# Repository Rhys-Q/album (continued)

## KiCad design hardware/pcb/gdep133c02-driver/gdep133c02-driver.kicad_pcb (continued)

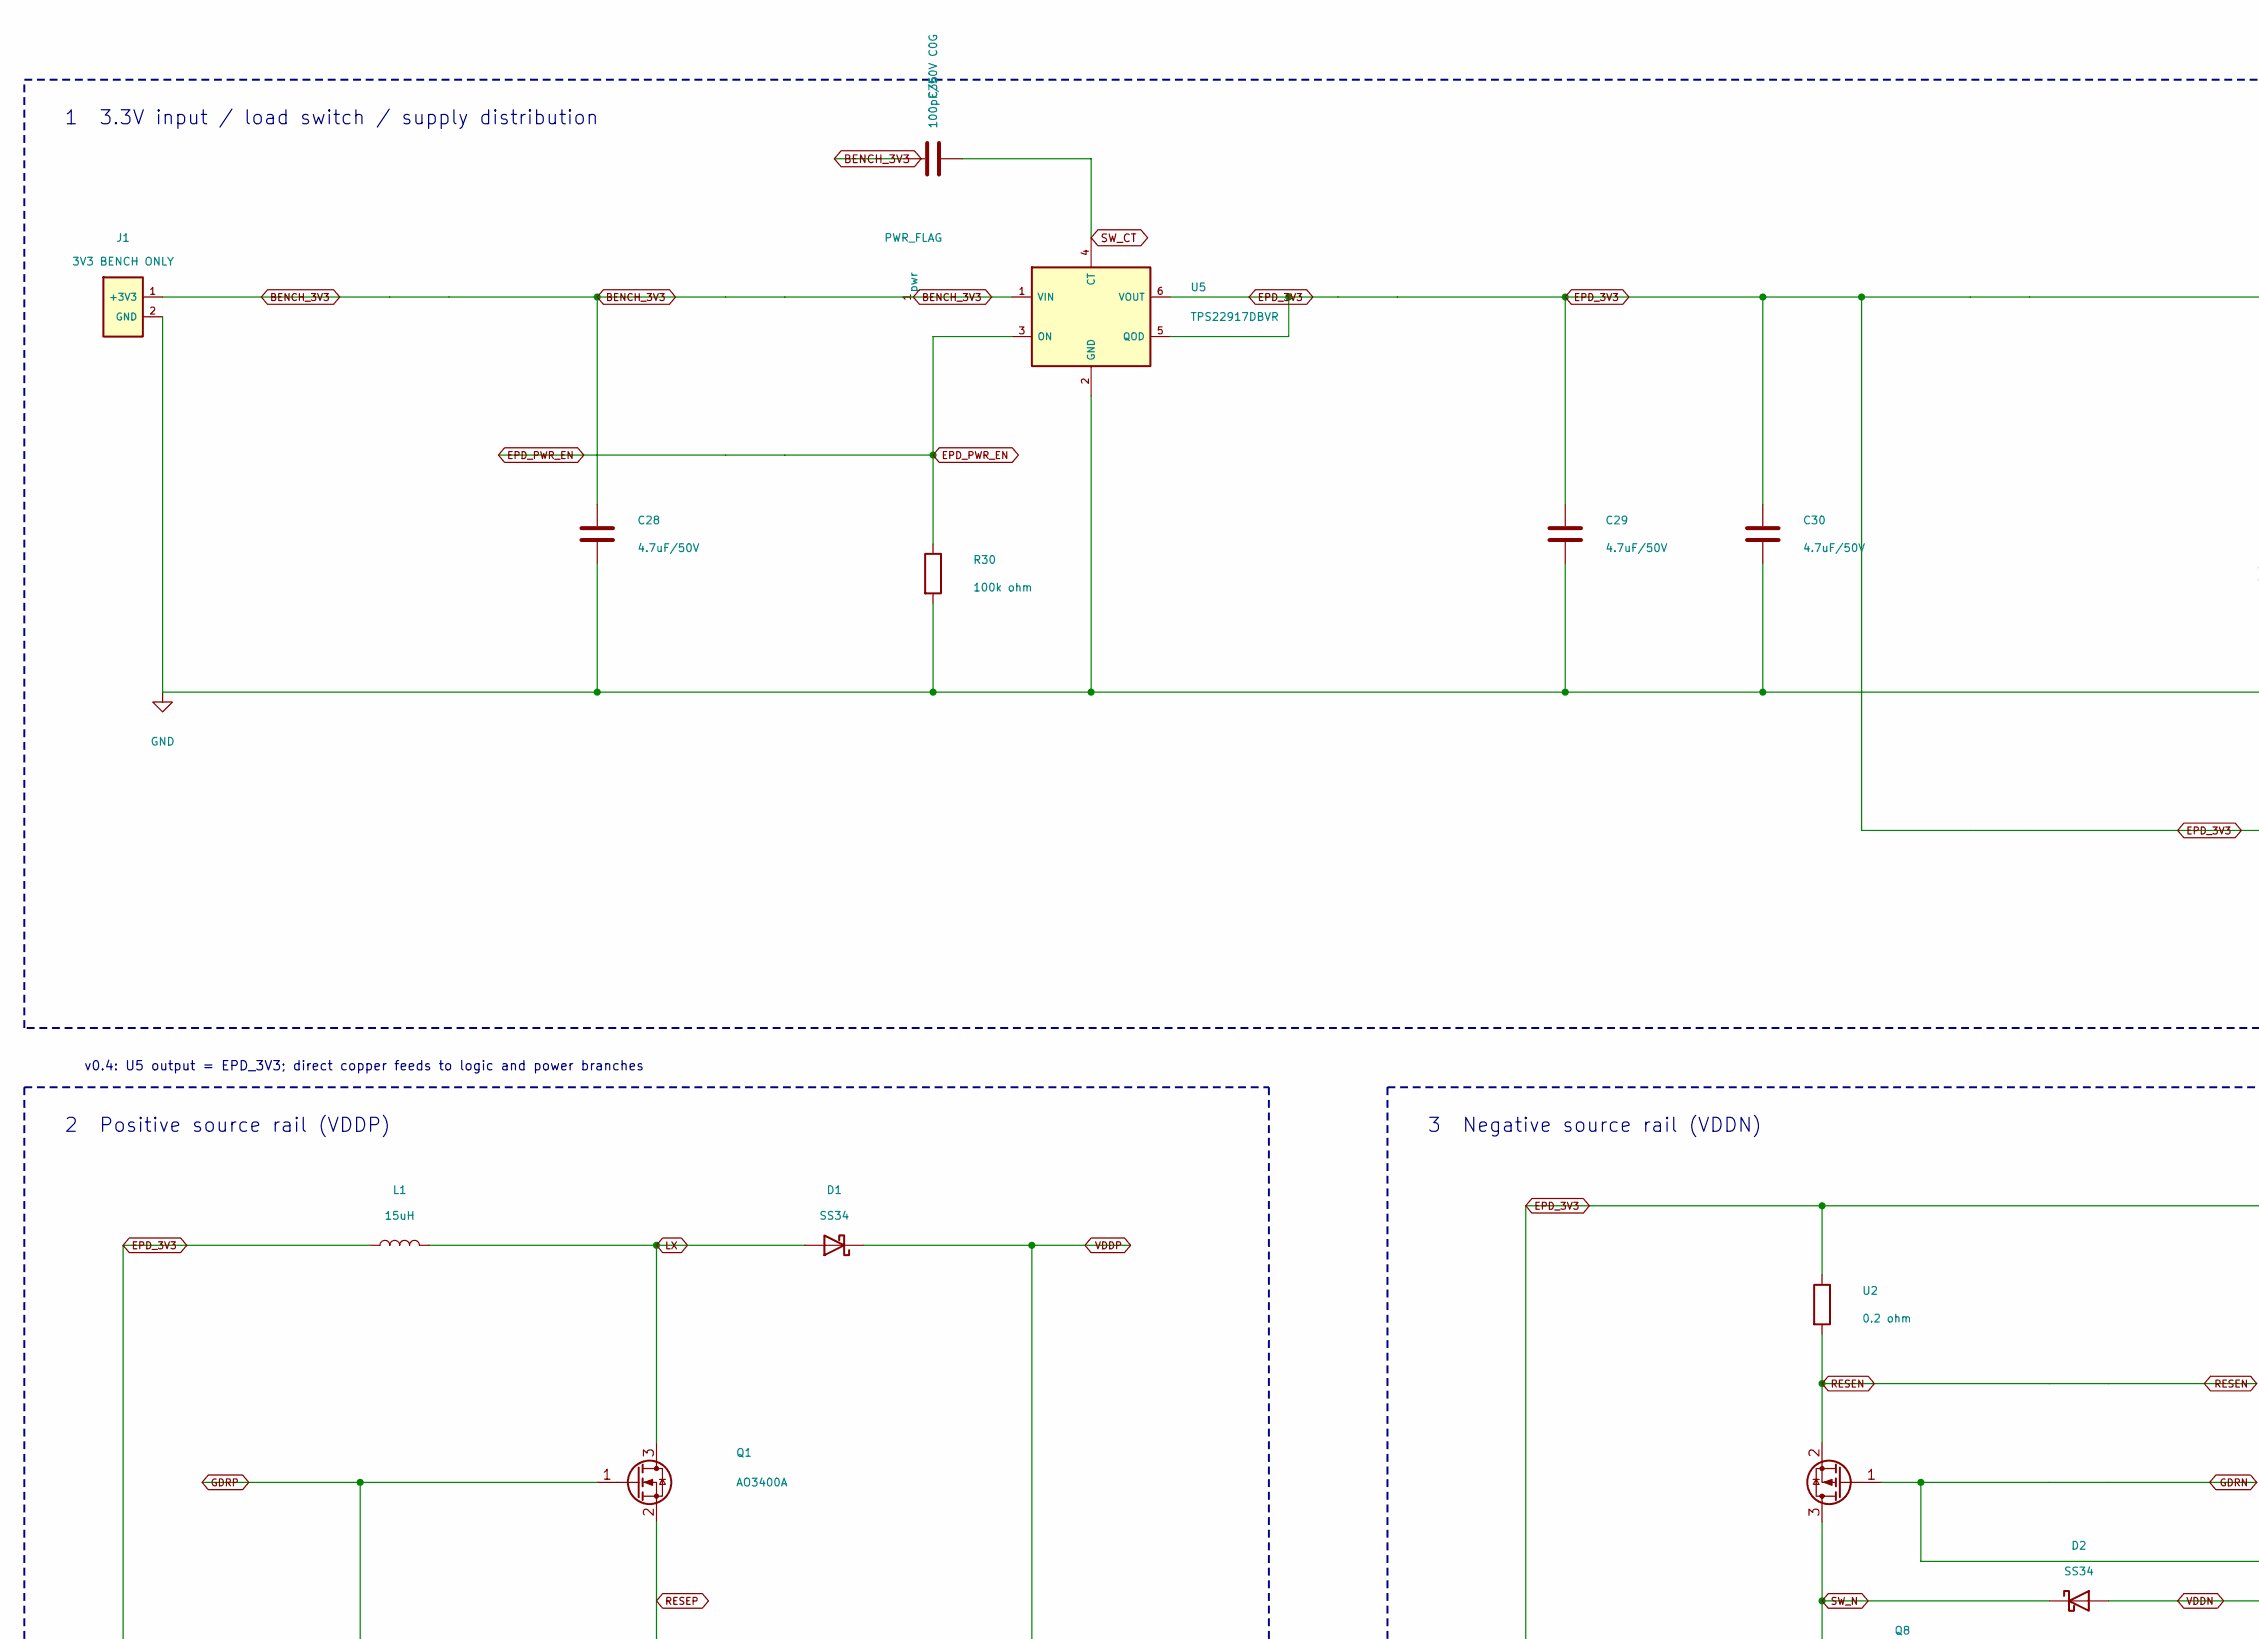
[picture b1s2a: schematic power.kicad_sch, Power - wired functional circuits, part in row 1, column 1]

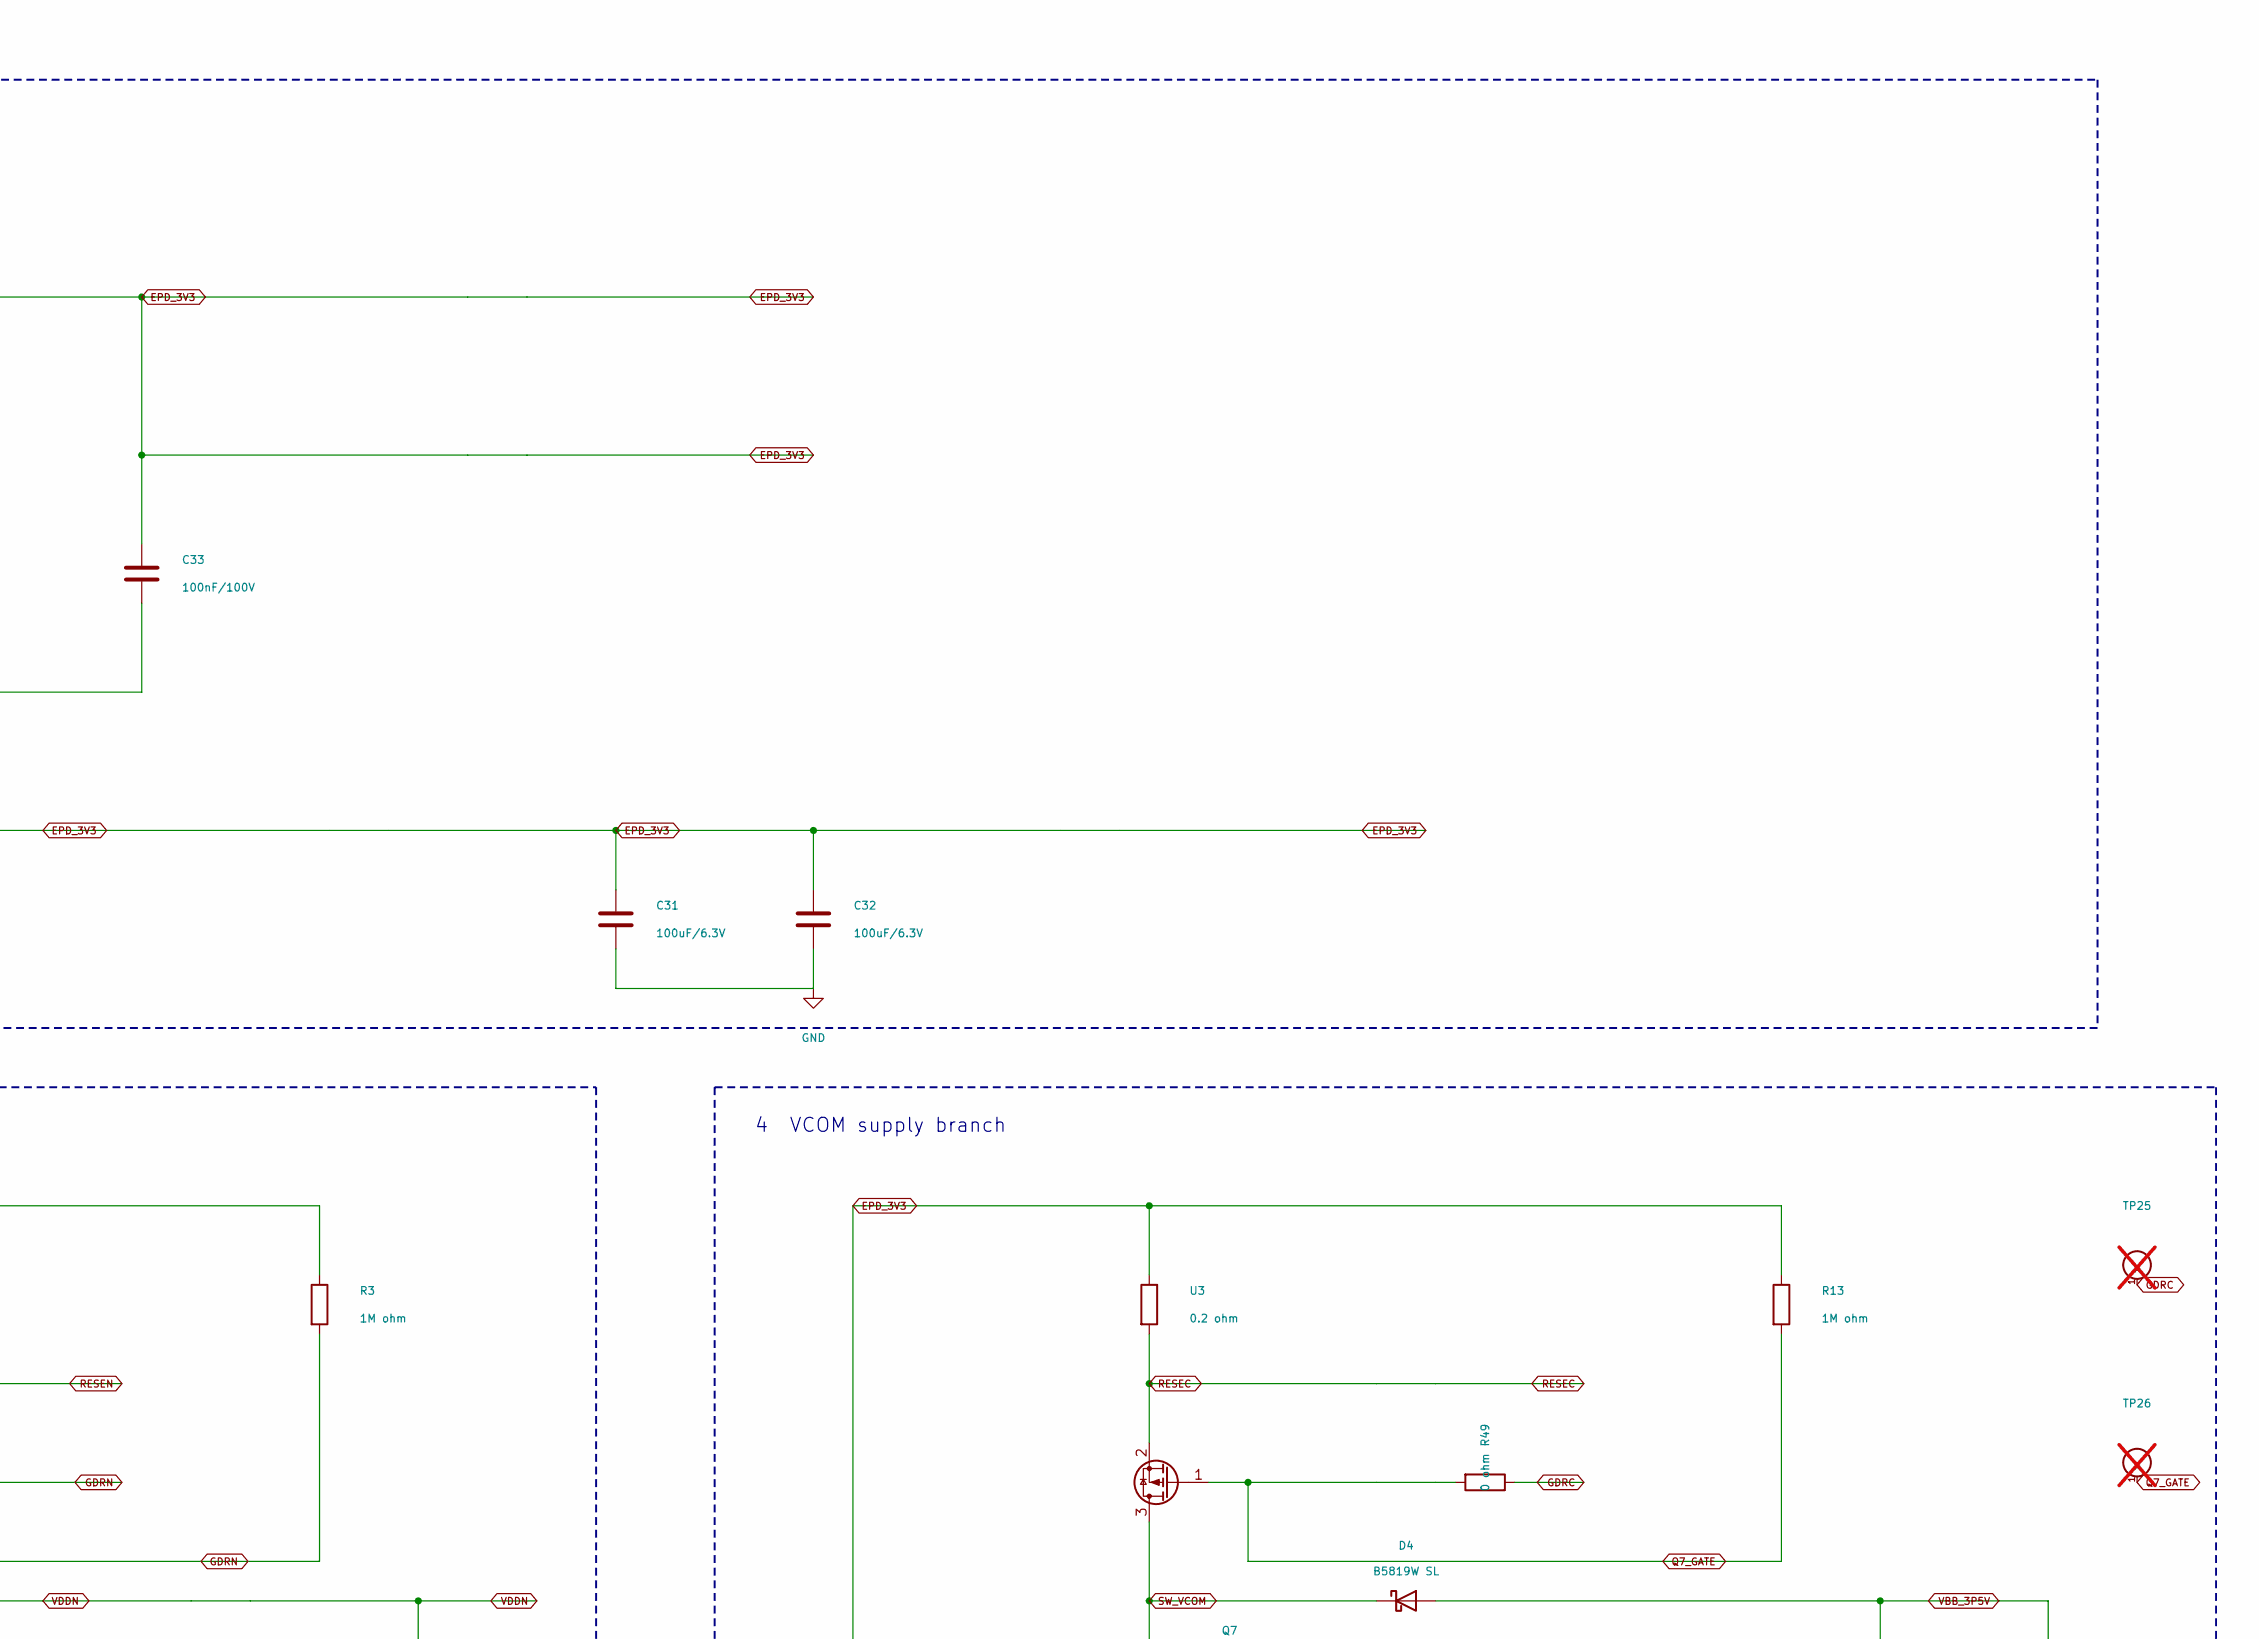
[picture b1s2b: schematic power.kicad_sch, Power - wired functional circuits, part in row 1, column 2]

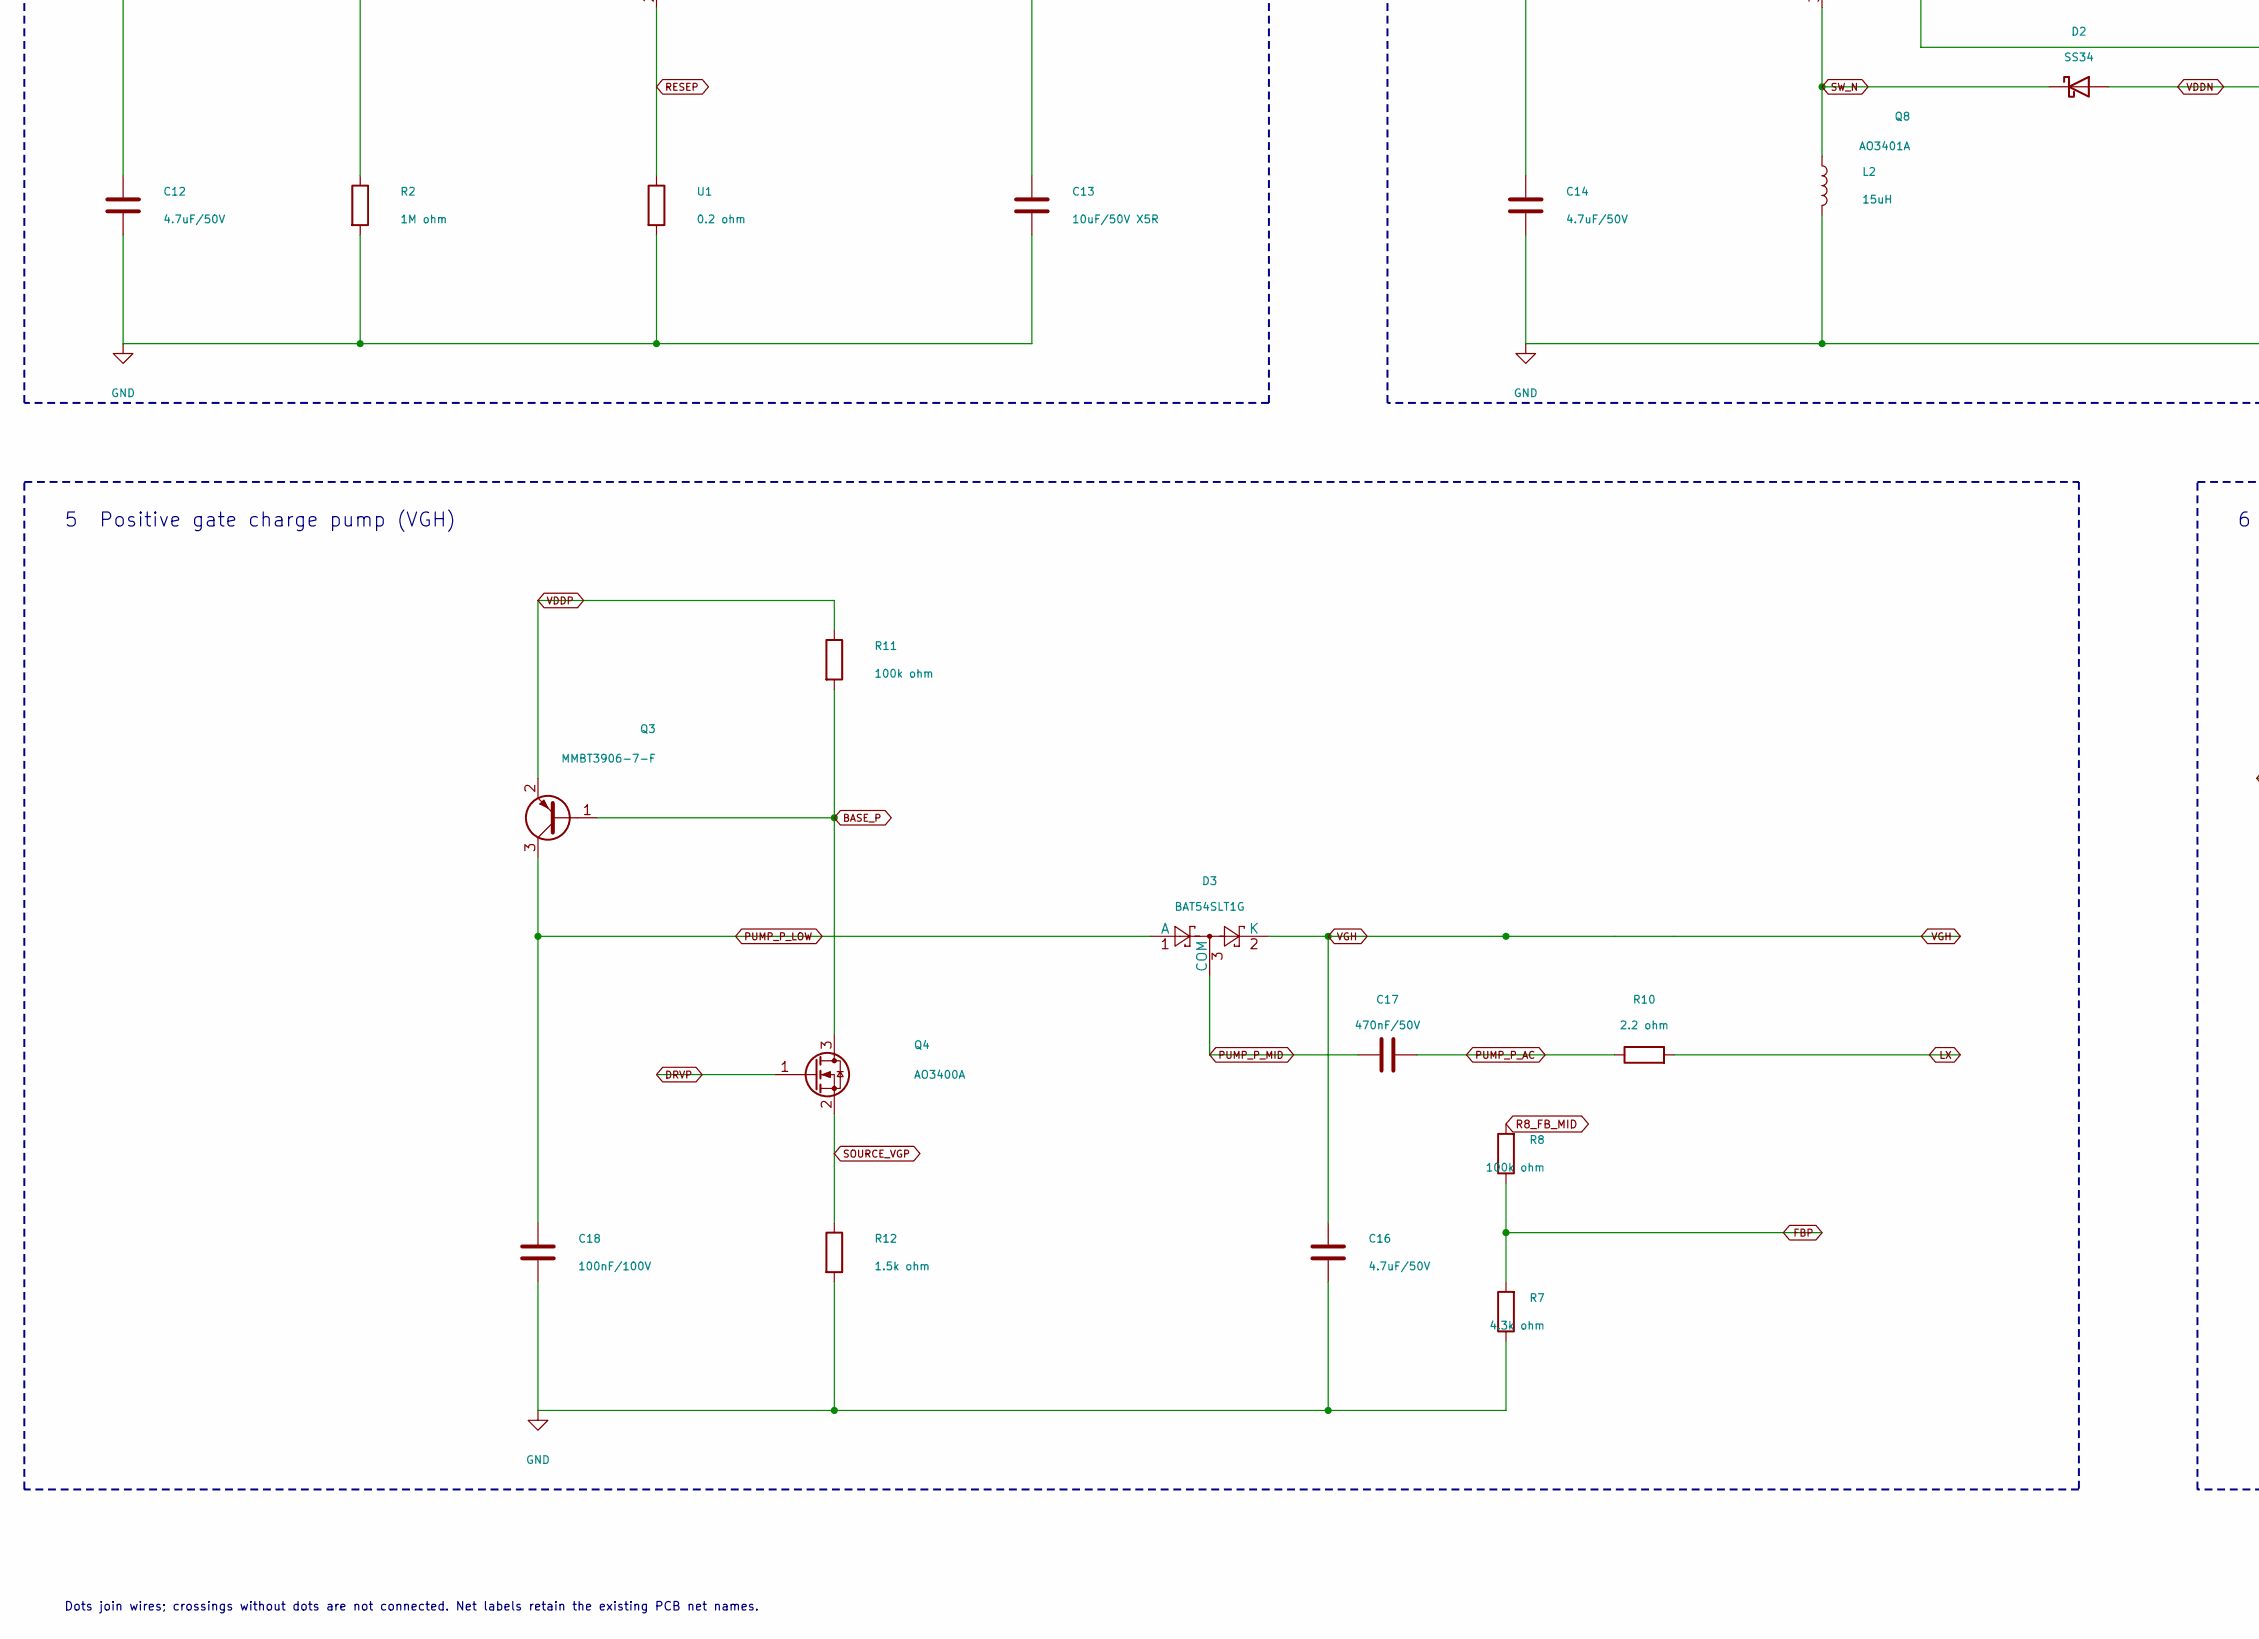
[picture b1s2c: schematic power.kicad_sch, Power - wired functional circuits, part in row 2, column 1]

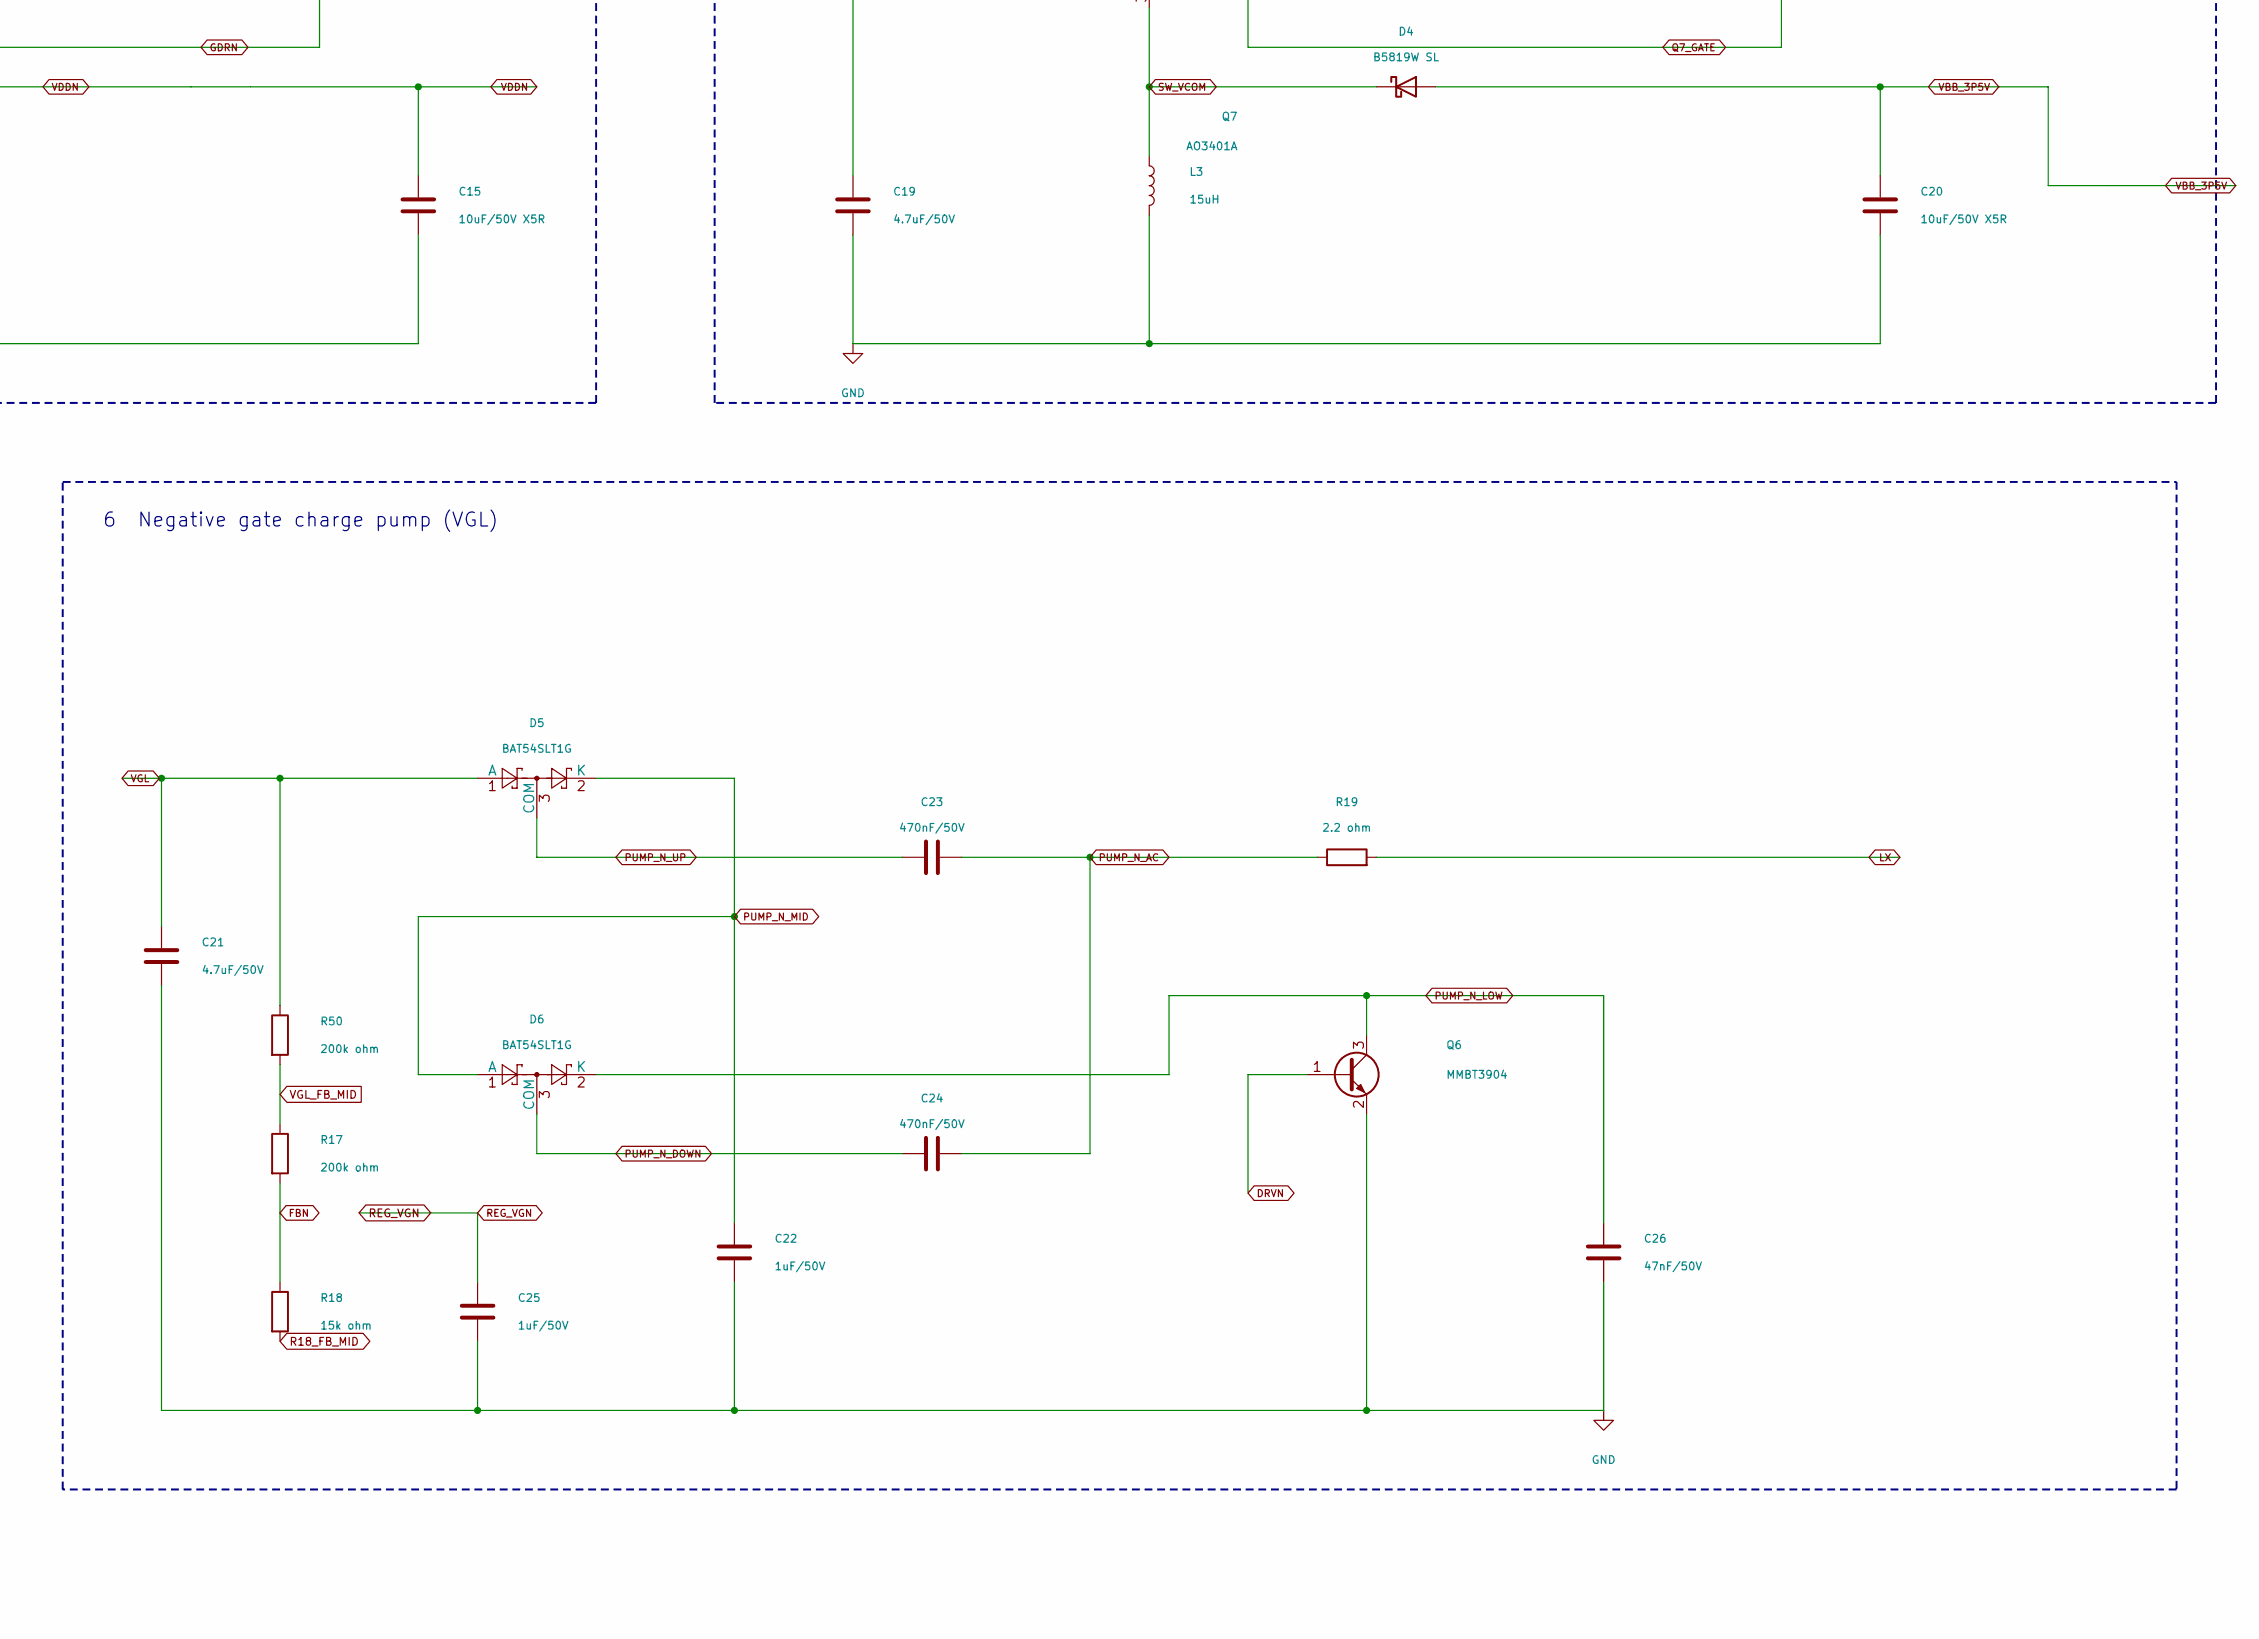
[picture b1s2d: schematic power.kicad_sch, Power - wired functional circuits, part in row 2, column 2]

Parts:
C12, C14, C16, C19, C21, C28, C29, C30: 4.7uF/50V; C_1206_HandSolder; MPN 1206B475K500NT; LCSC C29823
C13, C15, C20: 10uF/50V X5R; C_0805_HandSolder; MPN GRM21BR61H106KE43L; LCSC C440198
C17, C23, C24: 470nF/50V; C_0805_HandSolder; MPN CL21B474KBFNNNE; LCSC C13967
C18, C33: 100nF/100V; C_0805_HandSolder; MPN CL21B104KCFNNNE; LCSC C28233
C22, C25: 1uF/50V; C_0805_HandSolder; MPN CL21B105KBFNNNE; LCSC C28323
C26: 47nF/50V; Capacitor_SMD__C_0603_1608Metric; MPN CL10B473KB8NNNC; LCSC C1622
C31, C32: 100uF/6.3V; C_1206_HandSolder; MPN CL31A107MQHNNNE; LCSC C15008
C36: 100pF/50V C0G; Capacitor_SMD__C_0603_1608Metric; MPN CL10C101JB8NNNC; LCSC C14858
D1, D2: SS34; D_SMA_HandSolder; MPN SS34; LCSC C8678
D3, D5, D6: BAT54SLT1G; Package_TO_SOT_SMD__SOT-23; MPN BAT54SLT1G; LCSC C19726
D4: B5819W SL; Diode_SMD__D_SOD-123; MPN B5819W SL; LCSC C8598
J1: 3V3 BENCH ONLY; Connector_PinHeader_2.54mm__PinHeader_1x02_P2.54mm_Vertical; MPN TJC8-2.54-2A; LCSC C42410552
L1, L2, L3: 15uH; L_JIERR_PCR1040; MPN PCR1040-150-M; LCSC C53896892
Q1, Q4: AO3400A; Package_TO_SOT_SMD__SOT-23; MPN AO3400A; LCSC C20917
Q3: MMBT3906-7-F; Package_TO_SOT_SMD__SOT-23; MPN MMBT3906-7-F; LCSC C82762
Q6: MMBT3904; Package_TO_SOT_SMD__SOT-23; MPN MMBT3904(RANGE:100-300); LCSC C20526
Q7, Q8: AO3401A; Package_TO_SOT_SMD__SOT-23; MPN AO3401A; LCSC C15127
R2, R3, R13: 1M ohm; R_0805_HandSolder; MPN 0805W8F1004T5E; LCSC C17514
R7: 4.3k ohm; R_0805_HandSolder; MPN 0805W8F4301T5E; LCSC C17667
R8, R11, R30: 100k ohm; R_0805_HandSolder; MPN 0805W8F1003T5E; LCSC C149504
R10, R19: 2.2 ohm; R_0805_HandSolder; MPN 0805W8F220KT5E; LCSC C17521
R12: 1.5k ohm; R_0805_HandSolder; MPN 0805W8F1501T5E; LCSC C4310
R17, R50: 200k ohm; R_0805_HandSolder; MPN 0805W8F2003T5E; LCSC C17539
R18: 15k ohm; R_0805_HandSolder; MPN 0805W8F1502T5E; LCSC C17475
R49: 0 ohm; Resistor_SMD__R_0805_2012Metric; MPN 0805W8F0000T5E; LCSC C17477
TP25: GDRC; TestPoint__TestPoint_Pad_D1.5mm; MPN PCB test pad; not fitted
TP26: Q7_GATE; TestPoint__TestPoint_Pad_D1.5mm; MPN PCB test pad; not fitted
U1, U2, U3: 0.2 ohm; Resistor_SMD__R_1206_3216Metric; MPN WSL1206R2000FEA; LCSC C2073442
U5: TPS22917DBVR; Package_TO_SOT_SMD__SOT-23-6; MPN TPS22917DBVR; LCSC C2681320

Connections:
BASE_P: Q3.1 (B), Q4.3 (D), R11.2
BENCH_3V3: C28.1, C36.1, J1.1 (+3V3), U5.1 (VIN); also elsewhere on the board
DRVN: Q6.1 (B); also elsewhere on the board
DRVP: Q4.1 (G); also elsewhere on the board
EPD_3V3: C12.1, C14.1, C19.1, C29.1, C30.1, C31.1, C32.1, C33.1, L1.1, R3.1, R13.1, U2.1, U3.1, U5.5 (QOD), U5.6 (VOUT); also elsewhere on the board
EPD_PWR_EN: R30.1, U5.3 (ON); also elsewhere on the board
FBN: R17.2, R18.1; also elsewhere on the board
FBP: R7.2, R8.1; also elsewhere on the board
GDRC: R49.1, TP25.1 (1_1); also elsewhere on the board
GDRN: Q8.1 (G), R3.2; also elsewhere on the board
GDRP: Q1.1 (G), R2.1; also elsewhere on the board
GND: C12.2, C13.2, C14.2, C15.2, C16.2, C18.2, C19.2, C20.2, C21.2, C22.2, C25.2, C26.2, C28.2, C29.2, C30.2, C31.2, C32.2, C33.2, J1.2 (GND), L2.2, L3.2, Q6.2 (E), R2.2, R7.1, R12.2, R30.2, U1.2, U5.2 (GND); also elsewhere on the board
LX: D1.2 (A), L1.2, Q1.3 (D), R10.2, R19.2
PUMP_N_AC: C23.2, C24.2, R19.1
PUMP_N_DOWN: C24.1, D6.3 (COM)
PUMP_N_LOW: C26.1, D6.2 (K), Q6.3 (C)
PUMP_N_MID: C22.1, D5.2 (K), D6.1 (A)
PUMP_N_UP: C23.1, D5.3 (COM)
PUMP_P_AC: C17.2, R10.1
PUMP_P_LOW: C18.1, D3.1 (A), Q3.3 (C); also elsewhere on the board
PUMP_P_MID: C17.1, D3.3 (COM)
Q7_GATE: Q7.1 (G), R13.2, R49.2, TP26.1 (1_1)
R8_FB_MID: R8.2; also elsewhere on the board
R18_FB_MID: R18.2; also elsewhere on the board
REG_VGN: C25.1; also elsewhere on the board
RESEC: Q7.2 (S), U3.2; also elsewhere on the board
RESEN: Q8.2 (S), U2.2; also elsewhere on the board
RESEP: Q1.2 (S), U1.1; also elsewhere on the board
SOURCE_VGP: Q4.2 (S), R12.1
SW_CT: C36.2, U5.4 (CT); also elsewhere on the board
SW_N: D2.1 (K), L2.1, Q8.3 (D)
SW_VCOM: D4.1 (K), L3.1, Q7.3 (D)
VBB_3P5V: C20.1, D4.2 (A); also elsewhere on the board
VDDN: C15.1, D2.2 (A); also elsewhere on the board
VDDP: C13.1, D1.1 (K), Q3.2 (E), R11.1; also elsewhere on the board
VGH: C16.1, D3.2 (K); also elsewhere on the board
VGL: C21.1, D5.1 (A), R50.1; also elsewhere on the board
VGL_FB_MID: R17.1, R50.2

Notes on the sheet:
1 3.3V input / load switch / supply distribution
2 Positive source rail (VDDP)
3 Negative source rail (VDDN)
4 VCOM supply branch
5 Positive gate charge pump (VGH)
6 Negative gate charge pump (VGL)
Dots join wires; crossings without dots are not connected. Net labels retain the existing PCB net names.
v0.4: U5 output = EPD_3V3; direct copper feeds to logic and power branches
